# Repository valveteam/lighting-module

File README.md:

# lighting-module

This repository holds the KiCad design files for the light sensor module of the valve, containing the following:

* Schematics for the light sensor module.
* PCB design files for the light sensor module.
* Gerber and drill files required for manufacture of the PCB.

Notes:

* The circuit and PCB designs for this module currently use the STR05S3V3 Switching Regulator for voltage regulation ([datasheet here](https://docs-emea.rs-online.com/webdocs/150c/0900766b8150c4bd.pdf)). Due to supply issues, we had to move the voltage regulation to a different component, the TR05S3V3 ([datasheet here](https://docs-emea.rs-online.com/webdocs/150c/0900766b8150c31a.pdf)) and we have moved this circuitry to the [control module](https://github.com/valveteam/control-module).

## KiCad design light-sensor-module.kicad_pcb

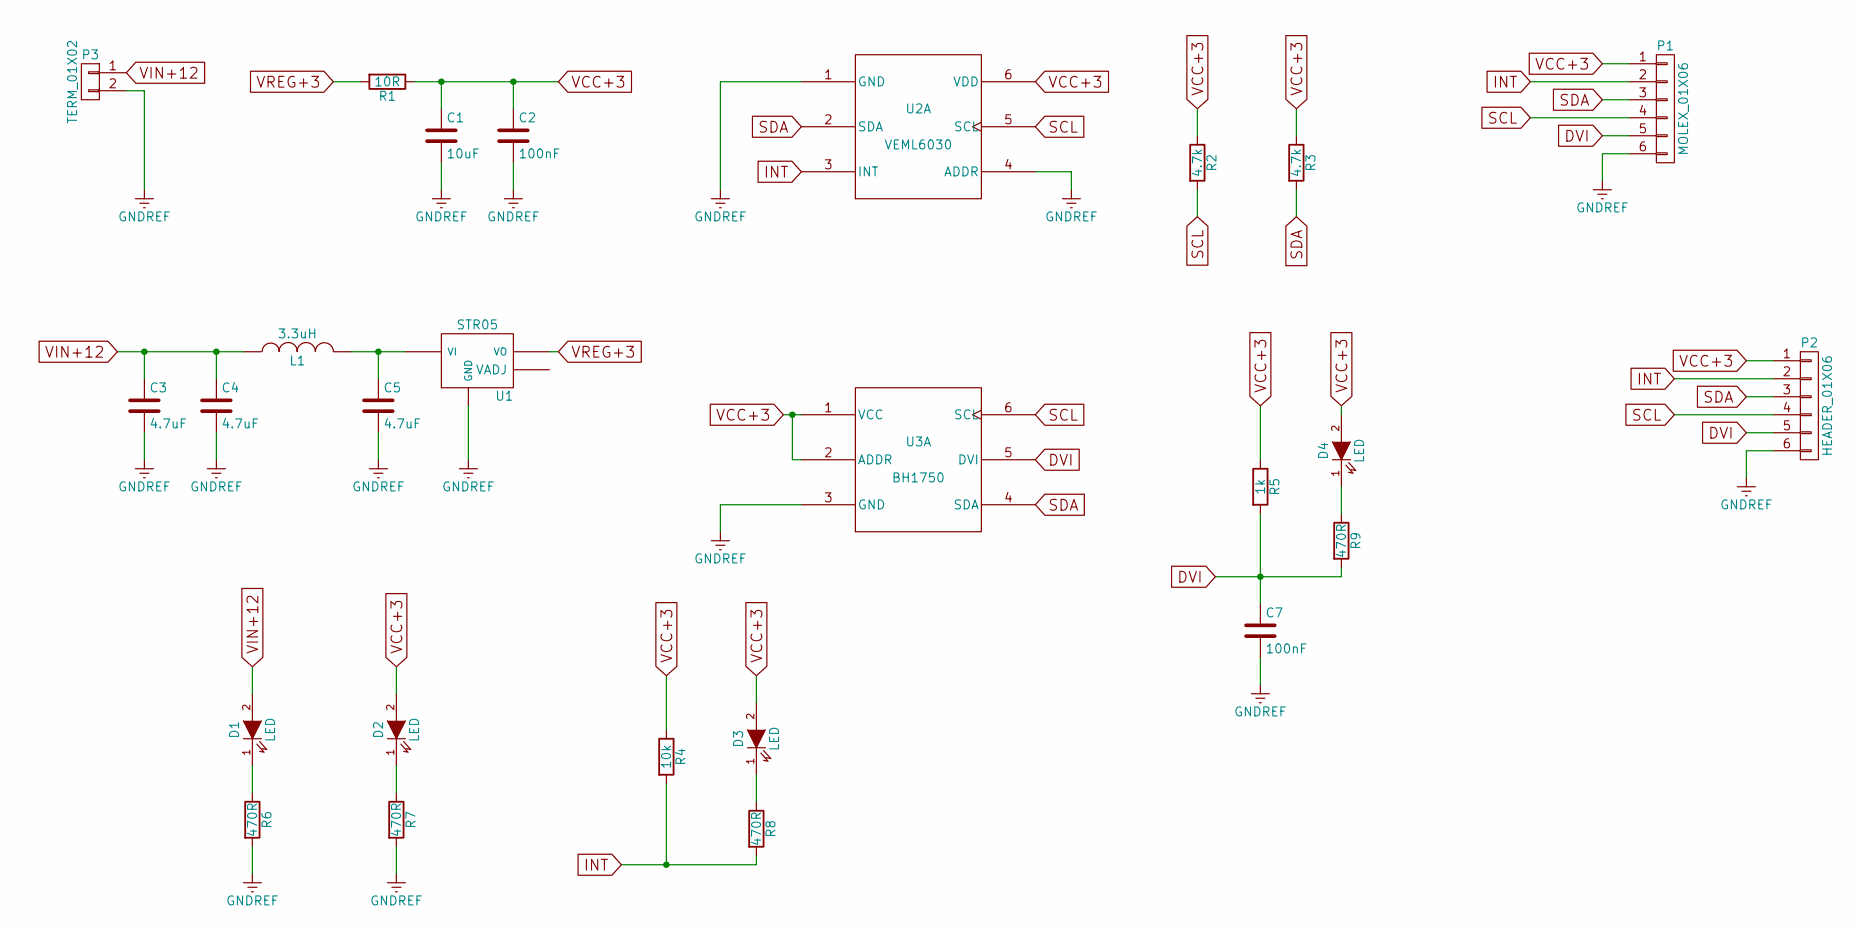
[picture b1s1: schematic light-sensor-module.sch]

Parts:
C1: 10uF; C_0805_HandSoldering
C2, C7: 100nF; C_0805_HandSoldering
C3, C4, C5: 4.7uF; C_0805_HandSoldering
D1, D2, D3, D4: LED; LED_0805_HandSoldering
L1: 3.3uH; WURTH_INDUCTOR
P1: MOLEX_01X06; Molex_KK-6410-06_06x2.54mm_Straight
P2: HEADER_01X06; Pin_Header_Straight_1x06_Pitch2.54mm
P3: TERM_01X02; TE_TERM
R1: 10R; R_0805_HandSoldering
R2, R3: 4.7k; R_0805_HandSoldering
R4: 10k; R_0805_HandSoldering
R5: 1k; R_0805_HandSoldering
R6, R7, R8, R9: 470R; R_0805_HandSoldering
U1: STR05
U2: VEML6030
U3: BH1750; WSOF6

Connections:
DVI: C7.1, P1.5, P2.5, R5.2, R9.2, U3.5 (DVI)
GNDREF: C1.2, C2.2, C3.2, C4.2, C5.2, C7.2, P1.6, P2.6, P3.2, R6.2, R7.2, U1.GND, U2.1 (GND), U2.4 (ADDR), U3.3 (GND)
INT: P1.2, P2.2, R4.2, R8.2, U2.3 (INT)
unnamed: C5.1, L1.2, U1.VI
unnamed: D1.1 (K), R6.1
unnamed: D2.1 (K), R7.1
unnamed: D3.1 (K), R8.1
unnamed: D4.1 (K), R9.1
SCL: P1.4, P2.4, R2.2, U2.5 (SCL), U3.6 (SCL)
SDA: P1.3, P2.3, R3.2, U2.2 (SDA), U3.4 (SDA)
VCC+3: C1.1, C2.1, D2.2 (A), D3.2 (A), D4.2 (A), P1.1, P2.1, R1.1, R2.1, R3.1, R4.1, R5.1, U2.6 (VDD), U3.1 (VCC), U3.2 (ADDR)
VIN+12: C3.1, C4.1, D1.2 (A), L1.1, P3.1
VREG+3: R1.2, U1.VO

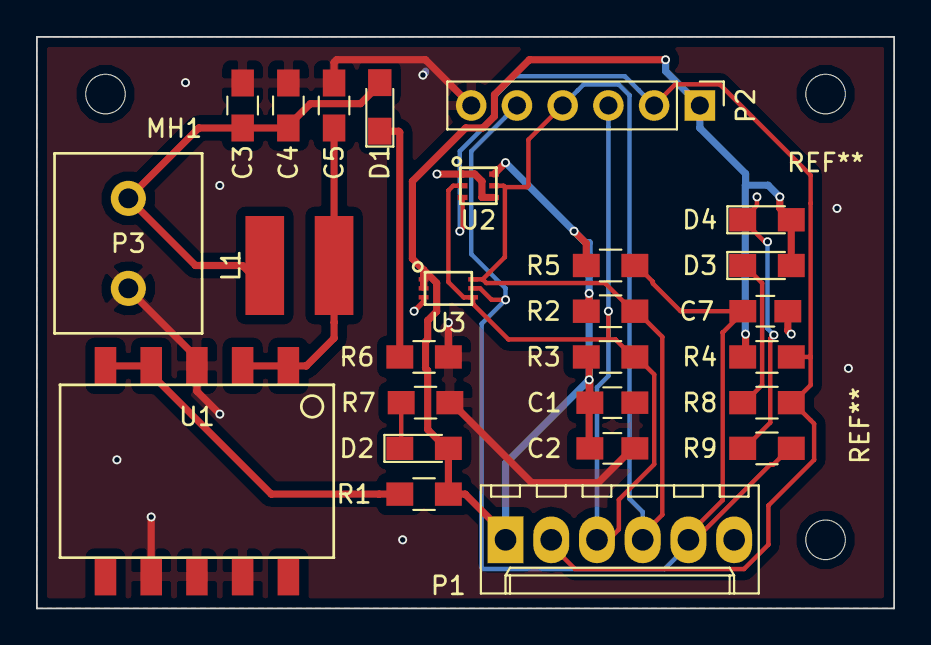
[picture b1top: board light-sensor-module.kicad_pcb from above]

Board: 2 copper layers, 47.6 x 31.8 mm, 27 parts (0 on the bottom side), 13 nets.

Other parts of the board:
MH1: MountingHole_2.2mm_M2

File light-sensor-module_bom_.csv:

Component,Description,Part,References,Value,Footprint,Quantity Per PCB,Datasheet
1,Unpolarized capacitor,C,C2 C7,100nF,C_0805_HandSoldering,2,
2,Unpolarized capacitor,C,C1,10uF,C_0805_HandSoldering,1,
3,Unpolarized capacitor,C,C3 C4 C5,4.7uF,C_0805_HandSoldering,3,
4,,LED-RESCUE-light-sensor-module,D1 D2 D3 D4,LED,LED_0805_HandSoldering,4,
5,,INDUCTOR,L1,3.3uH,WURTH_INDUCTOR,1,
6,,CONN_01X06,P2,HEADER_01X06,Pin_Header_Straight_1x06_Pitch2.54mm,1,
7,,CONN_01X06,P1,MOLEX_01X06,Molex_KK-6410-06_06x2.54mm_Straight,1,
8,,CONN_01X02,P3,TERM_01X02,TE_TERM,1,
9,Resistor,R,R1,10R,R_0805_HandSoldering,1,
10,Resistor,R,R4,10k,R_0805_HandSoldering,1,
11,Resistor,R,R5,1k,R_0805_HandSoldering,1,
12,Resistor,R,R2 R3,4.7k,R_0805_HandSoldering,2,
13,Resistor,R,R6 R7 R8 R9,470R,R_0805_HandSoldering,4,
14,,BH1750,U3,BH1750,WSOF6,1,
15,,STR05,U1,STR05,STR05,1,
16,,VEML6030,U2,VEML6030,VEML6030,1,





Component Groups:,16
Component Count:,26
Fitted Components:,26
Number of PCBs:,1
Total components:,26
Schematic Version:,
Schematic Date:,
BoM Date:,04/06/2018 09:53:13
Schematic Source:,C:/Users/tooyi/Dropbox/tfpb/lighting-module/light-sensor-module.sch
KiCad Version:,Eeschema 4.0.7

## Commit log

2018-05-22 Home computer branch
2018-05-23 Complete PCB design
2018-05-23 Add Gerbers, PDFs and Drill File
2018-06-04 Documentation
